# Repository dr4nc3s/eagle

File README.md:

# eagle #

My own Eagle components library as well as any PCB projects/designs I choose to work on. 

## Current Project - SAML21J breakout ##

Breakout board for using the SAML21J (yep, 64-pin). Currently putting together a list of features I want on the board. Don't want to make this too expensive, but I want enough features for me to utilize the various functions of the SAML21.

<h4>Features to Include</h4>
1. Power Supply : rails for 3.3V, 5V
2. microUSB port : for power input and programming
3. 10-pin JTAG header : for programming
4. External VREF circuitry : was told that internal VREF has a fair percentage error, so will want this out
5. Peripheral IO breakouts : breakouts specifically for some of the additional functions of the pins (I2C, UART, SPI, etc)
6. Status LEDs
7. USB-UART bridge (?) : unsure if I want this

## Future Projects ##

1. ESP32 breakout board (utilize WROOM module)
2. PIC breakout board - unsure whether I want PIC18, PIC24, or PIC32 architecture
3.

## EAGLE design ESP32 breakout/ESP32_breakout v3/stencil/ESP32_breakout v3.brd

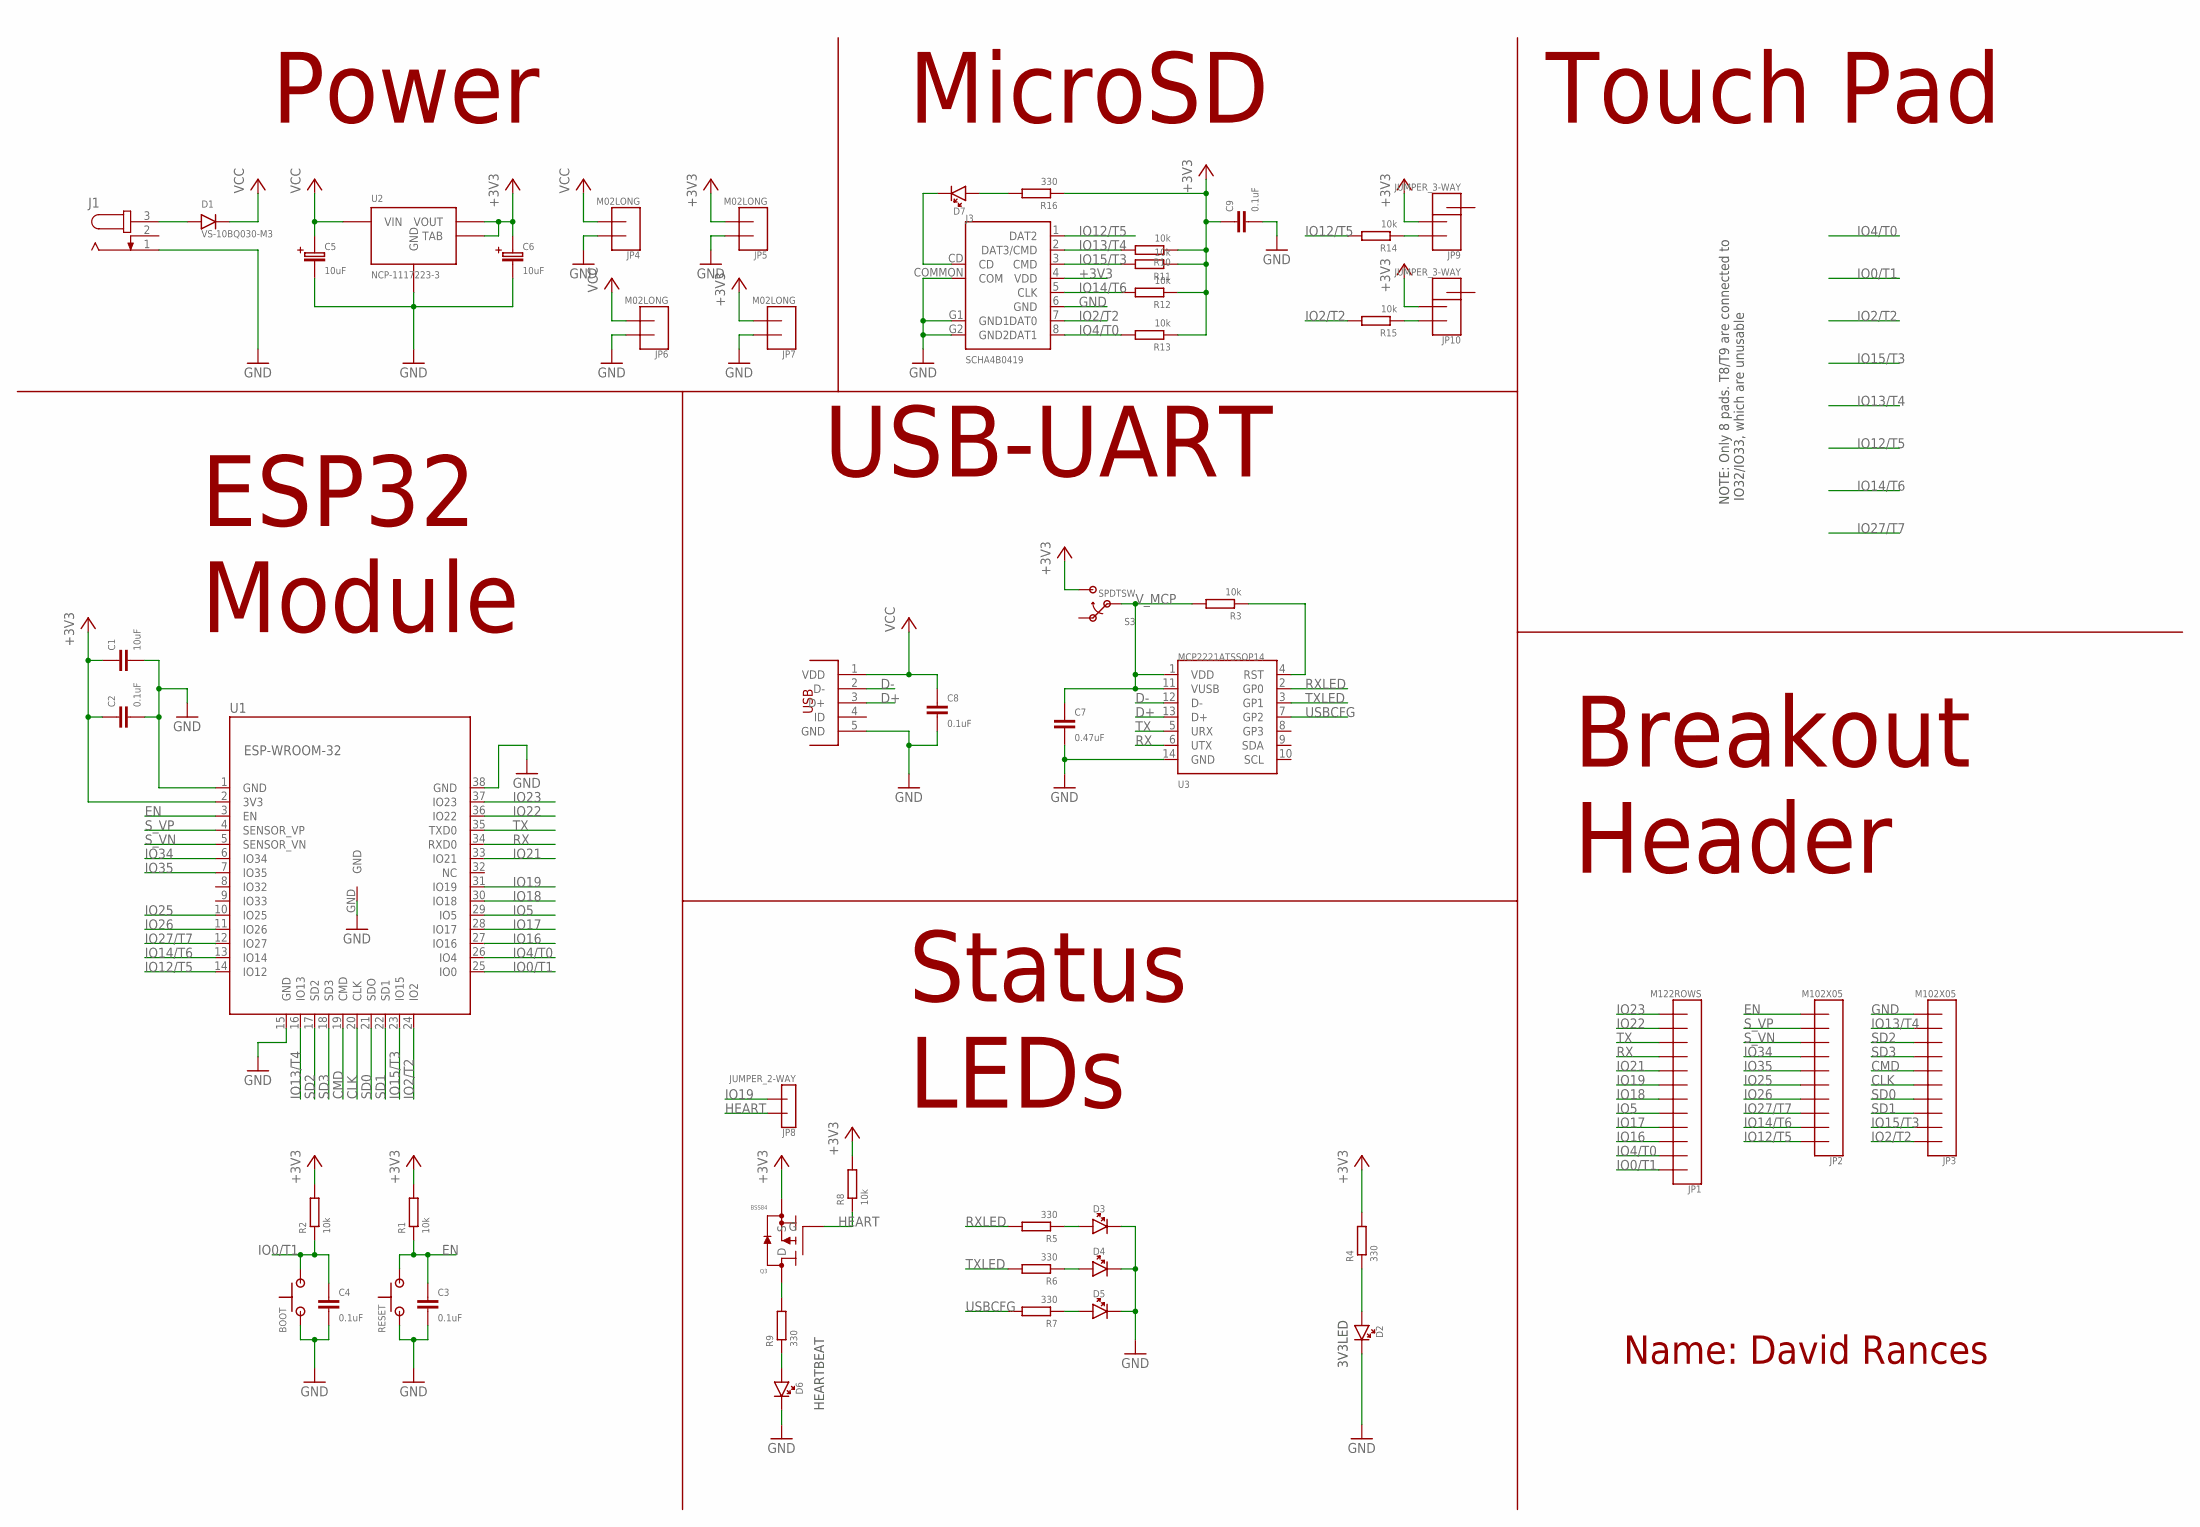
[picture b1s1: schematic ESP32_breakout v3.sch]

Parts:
BOOT: PUSHBUTTONSKHMQME010; SKHMQME010
C1: 10uF; CAP-0603
C2, C3, C4, C8, C9: 0.1uF; CAP-0603
C5, C6: 10uF; B-3528
C7: 0.47uF; CAP-0603
D1: VS-10BQ030-M3; DO-214AA
D2, D3, D4, D5, D6, D7: LED1206; LED-1206
J1: JACK-PLUG0; SPC4077
J3: SCHA4B0419; MICROSD_SCHA4B0419
JP1: M122ROWS; 2X06
JP2, JP3: M102X05; 2X05
JP4, JP5, JP6, JP7: M02LONG; 1X02-LONG
JP8: JUMPER_2-WAY; 1X02
JP9, JP10: JUMPER_3-WAY; 1X03
Q3: BSS84; SOT-23-3
R1, R2, R3, R8, R10, R11, R12, R13, R14, R15: 10k; RES-0603
R4, R5, R6, R7, R9, R16: 330; RES-0603
RESET: PUSHBUTTONSKHMQME010; SKHMQME010
S3: SPDTSW; SPDT_TH
U1: ESP-WROOM-32
U2: NCP-1117223-3; SOT-223-3
U3: MCP2221ATSSOP14; TSSOP-14
U$4: MOLEX_USBMICRO; MOLEX_47346-001

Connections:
+3V3: C1.1, C2.1, C6.P, C9.1, J3.4 (VDD), JP5.2, JP7.2, JP9.2, JP10.2, Q3.S, R1.2, R2.2, R4.2, R8.2, R10.1, R11.1, R12.1, R13.1, R16.1, S3.3 (2), U1.2 (3V3), U2.2 (VOUT), U2.PAD (TAB)
CLK: JP3.5, U1.20 (CLK)
CMD: JP3.6, U1.19 (CMD)
D+: U3.13 (D+), U$4.3 (D+)
D-: U3.12 (D-), U$4.2 (D-)
EN: C3.1, JP2.10, R1.1, RESET.3 (2), RESET.4 (2), U1.3 (EN)
GND: BOOT.1, BOOT.2 (1), C1.2, C2.2, C3.2, C4.2, C5.N, C6.N, C7.2, C8.2, C9.2, D2.C, D3.C, D4.C, D5.C, D6.C, J1.1, J3.6 (GND), J3.COMMON (COM), J3.G1 (GND1), J3.G2 (GND2), JP3.10, JP4.1, JP5.1, JP6.1, JP7.1, RESET.1, RESET.2 (1), U1.1 (GND), U1.15 (GND), U1.38 (GND), U1.GND, U2.1 (GND), U3.14 (GND), U$4.5 (GND)
HEART: JP8.1, Q3.G, R8.1
IO0/T1: BOOT.3 (2), BOOT.4 (2), C4.1, JP1.1, R2.1, U1.25 (IO0)
IO2/T2: J3.7 (DAT0), JP3.1, R15.2, U1.24 (IO2)
IO4/T0: J3.8 (DAT1), JP1.2, R13.2, U1.26 (IO4)
IO5: JP1.5, U1.29 (IO5)
IO12/T5: J3.1 (DAT2), JP2.1, R14.2, U1.14 (IO12)
IO13/T4: J3.2 (DAT3/CMD), JP3.9, R10.2, U1.16 (IO13)
IO14/T6: J3.5 (CLK), JP2.2, R12.2, U1.13 (IO14)
IO15/T3: J3.3 (CMD), JP3.2, R11.2, U1.23 (IO15)
IO16: JP1.3, U1.27 (IO16)
IO17: JP1.4, U1.28 (IO17)
IO18: JP1.6, U1.30 (IO18)
IO19: JP1.7, JP8.2, U1.31 (IO19)
IO21: JP1.8, U1.33 (IO21)
IO22: JP1.11, U1.36 (IO22)
IO23: JP1.12, U1.37 (IO23)
IO25: JP2.5, U1.10 (IO25)
IO26: JP2.4, U1.11 (IO26)
IO27/T7: JP2.3, U1.12 (IO27)
IO34: JP2.7, U1.6 (IO34)
IO35: JP2.6, U1.7 (IO35)
unnamed: D1.A, J1.3
unnamed: R3.1, U3.4 (RST)
unnamed: D5.A, R7.1
unnamed: D2.A, R4.1
unnamed: JP9.1, R14.1
unnamed: JP10.1, R15.1
unnamed: D3.A, R5.1
unnamed: D6.A, R9.1
unnamed: Q3.D, R9.2
unnamed: D4.A, R6.1
unnamed: D7.C, J3.CD
unnamed: D7.A, R16.2
RX: JP1.9, U1.34 (RXD0), U3.6 (UTX)
RXLED: R5.2, U3.2 (GP0)
SD0: JP3.4, U1.21 (SDO)
SD1: JP3.3, U1.22 (SD1)
SD2: JP3.8, U1.17 (SD2)
SD3: JP3.7, U1.18 (SD3)
S_VN: JP2.8, U1.5 (SENSOR_VN)
S_VP: JP2.9, U1.4 (SENSOR_VP)
TX: JP1.10, U1.35 (TXD0), U3.5 (URX)
TXLED: R6.2, U3.3 (GP1)
USBCFG: R7.2, U3.7 (GP2)
VCC: C5.P, C8.1, D1.C, JP4.2, JP6.2, U2.3 (VIN), U$4.1 (VDD)
V_MCP: C7.1, R3.2, S3.2 (OUT), U3.1 (VDD), U3.11 (VUSB)

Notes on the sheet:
NOTE: Only 8 pads. T8/T9 are connected to IO32/IO33, which are unusable
3V3LED
HEARTBEAT
Power
MicroSD
Touch Pad
ESP32 Module
Status LEDs
Breakout Header
USB-UART
Name: David Rances

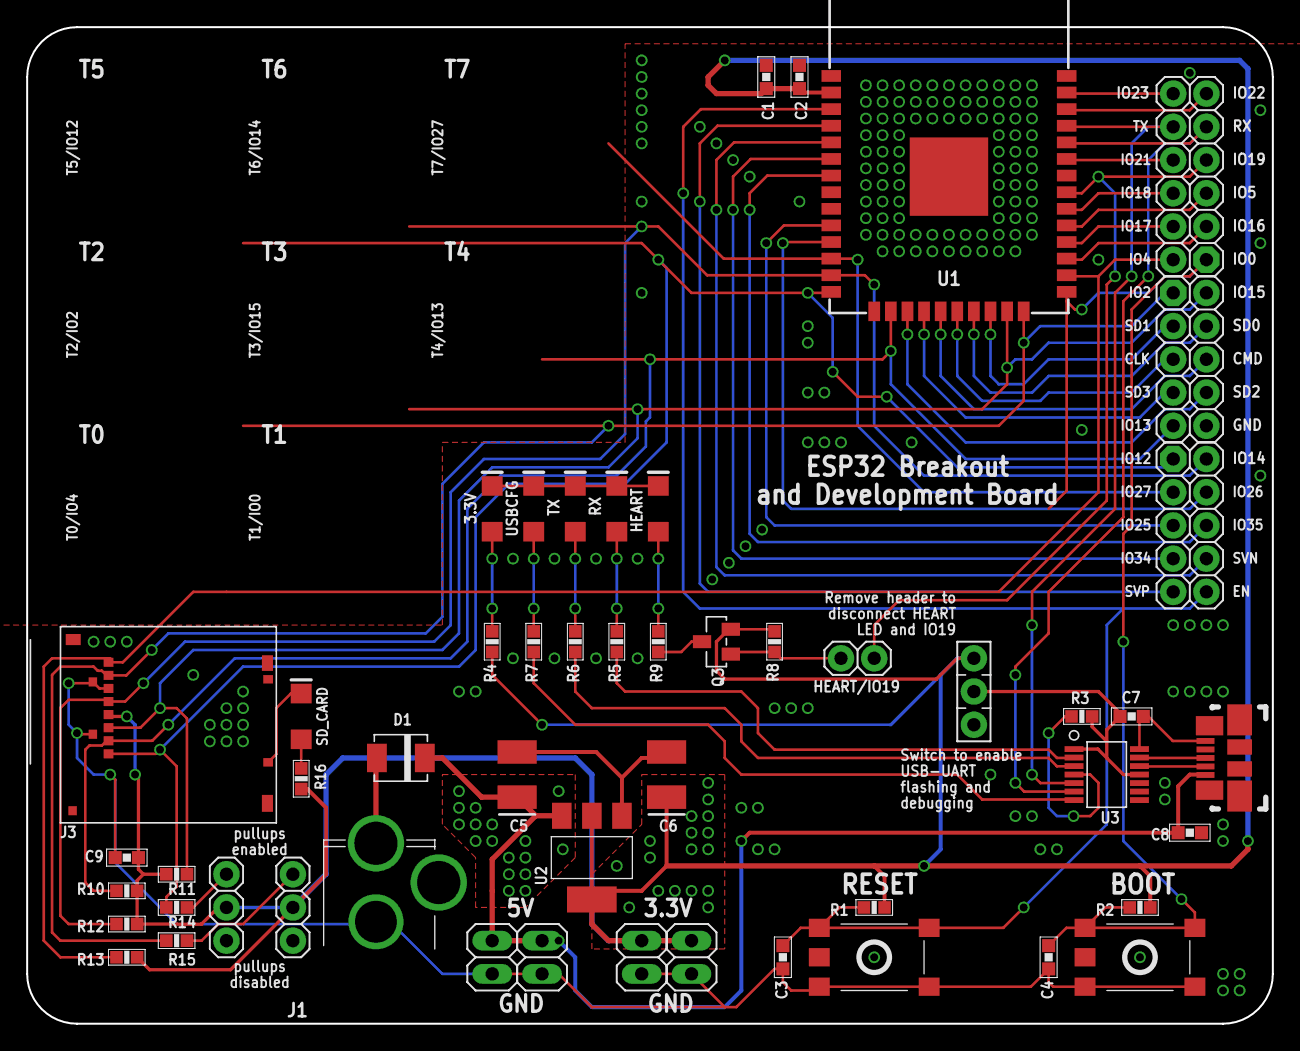
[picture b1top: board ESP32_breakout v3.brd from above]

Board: 2 copper layers, 95.2 x 76.2 mm, 52 parts (0 on the bottom side), 53 nets.

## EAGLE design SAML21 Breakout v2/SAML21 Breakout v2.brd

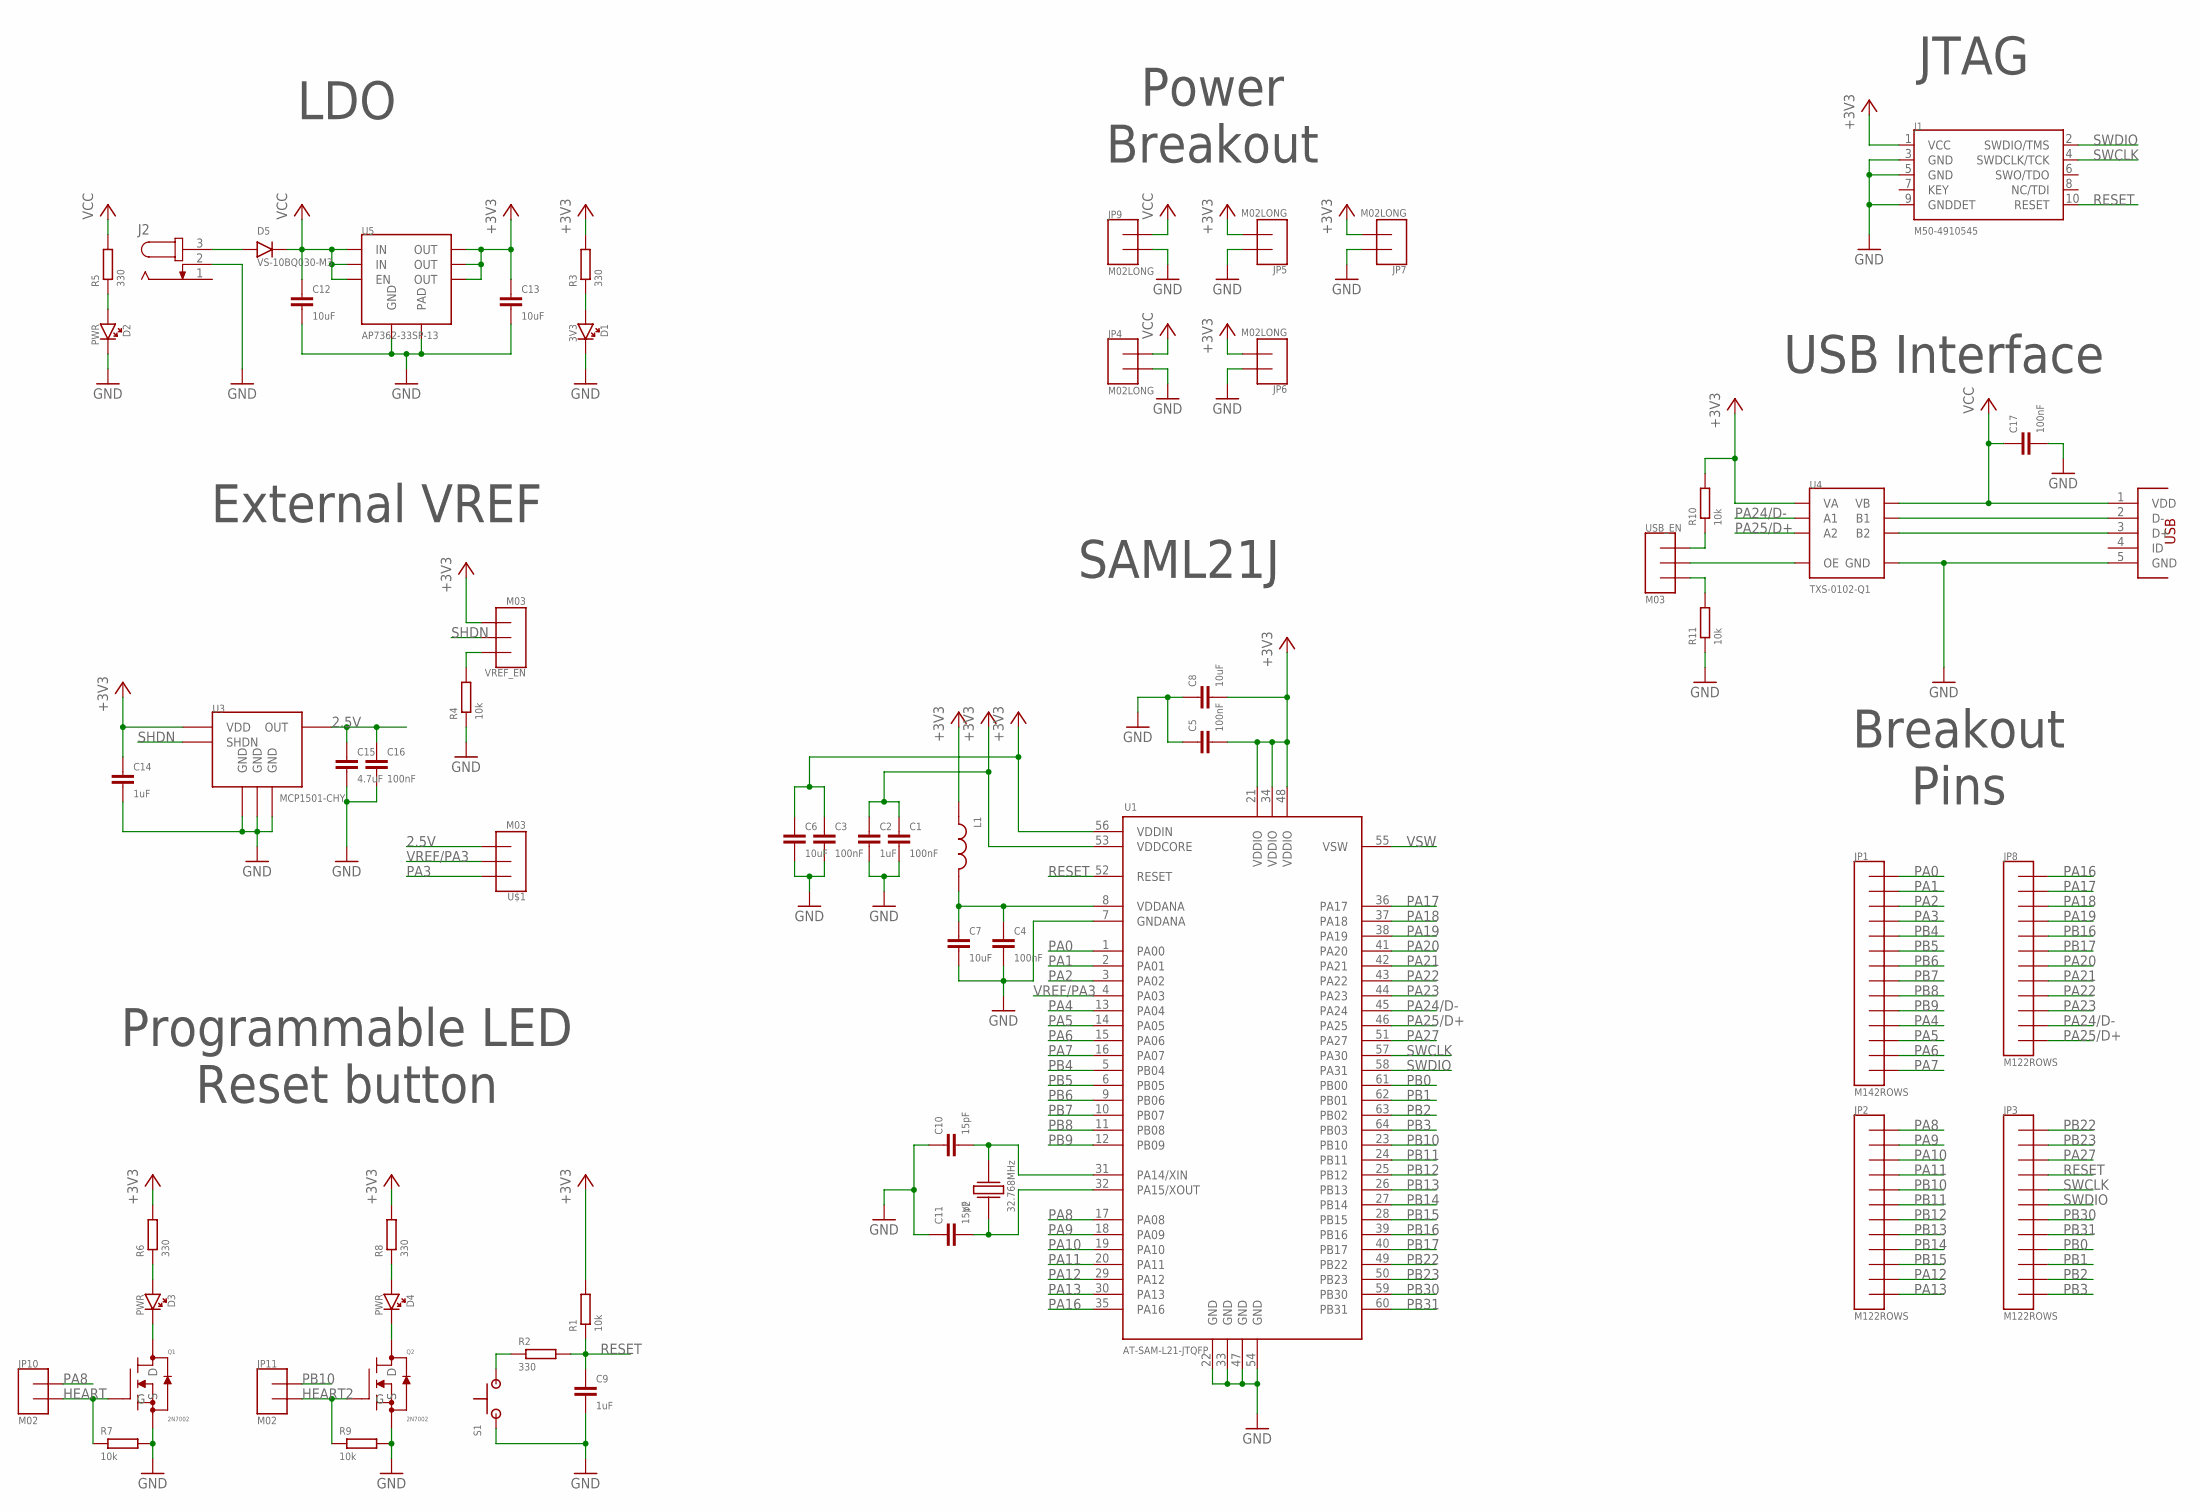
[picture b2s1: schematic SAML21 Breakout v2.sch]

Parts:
C1, C3, C4, C5, C16, C17: 100nF; CAP-0603
C2, C9, C14: 1uF; CAP-0603
C6, C7, C8, C12, C13: 10uF; CAP-0603
C10, C11: 15pF; CAP-0603
C15: 4.7uF; CAP-0805
D1: 3V3; LED-1206
D2, D3, D4: PWR; LED-1206
D5: VS-10BQ030-M3; DO-214AA
J1: M50-4910545
J2: JACK-PLUG0; SPC4077
JP1: M142ROWS; 2X07
JP2, JP3, JP8: M122ROWS; 2X06
JP4, JP5, JP6, JP7, JP9: M02LONG; 1X02-LONG
JP10, JP11: M02; 1X02
L1: INDUCTOR0603; IND-0603
Q1, Q2: 2N7002; SOT-23-3
R1, R4, R7, R9, R10, R11: 10k; RES-0805
R2, R3, R5, R6, R8: 330; RES-0805
S1: SKHMQME010
U1: AT-SAM-L21-JTQFP; TQFP-64
U3: MCP1501-CHY; SOT-23-6
U4: TXS-0102-Q1; VSSOP-8
U5: AP7362-33SP-13; SO-8EP
U$1: M03; 1X03
U$6: MOLEX_USBMICRO; MOLEX_47346-001
USB_EN: M03; 1X03
VREF_EN: M03; 1X03
Y2: 32.768MHz; CFPX-217

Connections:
2.5V: C15.1, C16.1, U3.1 (OUT), U$1.3
+3V3: C1.1, C2.1, C3.1, C5.2, C6.1, C8.2, C13.1, C14.1, J1.1 (VCC), JP5.2, JP6.2, JP7.2, L1.1, R1.2, R3.2, R6.2, R8.2, R10.2, U1.21 (VDDIO), U1.34 (VDDIO), U1.48 (VDDIO), U1.53 (VDDCORE), U1.56 (VDDIN), U3.6 (VDD), U4.3 (VA), U5.5 (OUT), U5.6 (OUT), U5.7 (OUT), VREF_EN.3
GND: C1.2, C2.2, C3.2, C4.2, C5.1, C6.2, C7.2, C8.1, C9.2, C10.1, C11.1, C12.2, C13.2, C14.2, C15.2, C16.2, C17.2, D1.C, D2.C, J1.3 (GND), J1.5 (GND), J1.9 (GNDDET), J2.2, JP4.2, JP5.1, JP6.1, JP7.1, JP9.2, Q1.S, Q2.S, R4.1, R7.2, R9.2, R11.1, S1.1, U1.7 (GNDANA), U1.22 (GND), U1.33 (GND), U1.47 (GND), U1.54 (GND), U3.2 (GND), U3.3 (GND), U3.5 (GND), U4.2 (GND), U5.1 (GND), U5.PAD, U$6.5 (GND)
HEART: JP10.2, Q1.G, R7.1
HEART2: JP11.2, Q2.G, R9.1
unnamed: R2.1, S1.3 (2)
unnamed: D1.A, R3.1
unnamed: C4.1, C7.1, L1.2, U1.8 (VDDANA)
unnamed: C10.2, U1.31 (PA14/XIN), Y2.2
unnamed: C11.2, U1.32 (PA15/XOUT), Y2.1
unnamed: D2.A, R5.1
unnamed: R4.2, VREF_EN.1
unnamed: D3.A, R6.1
unnamed: D3.C, Q1.D
unnamed: D4.A, R8.1
unnamed: D4.C, Q2.D
unnamed: D5.A, J2.3
unnamed: R10.1, USB_EN.1
unnamed: U4.8 (B1), U$6.2 (D-)
unnamed: U4.1 (B2), U$6.3 (D+)
unnamed: R11.2, USB_EN.3
unnamed: U4.6 (OE), USB_EN.2
PA0: JP1.1, U1.1 (PA00)
PA1: JP1.2, U1.2 (PA01)
PA2: JP1.3, U1.3 (PA02)
PA3: JP1.4, U$1.1
PA4: JP1.11, U1.13 (PA04)
PA5: JP1.12, U1.14 (PA05)
PA6: JP1.13, U1.15 (PA06)
PA7: JP1.14, U1.16 (PA07)
PA8: JP2.1, JP10.1, U1.17 (PA08)
PA9: JP2.2, U1.18 (PA09)
PA10: JP2.3, U1.19 (PA10)
PA11: JP2.4, U1.20 (PA11)
PA12: JP2.11, U1.29 (PA12)
PA13: JP2.12, U1.30 (PA13)
PA16: JP8.1, U1.35 (PA16)
PA17: JP8.2, U1.36 (PA17)
PA18: JP8.3, U1.37 (PA18)
PA19: JP8.4, U1.38 (PA19)
PA20: JP8.7, U1.41 (PA20)
PA21: JP8.8, U1.42 (PA21)
PA22: JP8.9, U1.43 (PA22)
PA23: JP8.10, U1.44 (PA23)
PA24/D-: JP8.11, U1.45 (PA24), U4.5 (A1)
PA25/D+: JP8.12, U1.46 (PA25), U4.4 (A2)
PA27: JP3.3, U1.51 (PA27)
PB0: JP3.9, U1.61 (PB00)
PB1: JP3.10, U1.62 (PB01)
PB2: JP3.11, U1.63 (PB02)
PB3: JP3.12, U1.64 (PB03)
PB4: JP1.5, U1.5 (PB04)
PB5: JP1.6, U1.6 (PB05)
PB6: JP1.7, U1.9 (PB06)
PB7: JP1.8, U1.10 (PB07)
PB8: JP1.9, U1.11 (PB08)
PB9: JP1.10, U1.12 (PB09)
PB10: JP2.5, JP11.1, U1.23 (PB10)
PB11: JP2.6, U1.24 (PB11)
PB12: JP2.7, U1.25 (PB12)
PB13: JP2.8, U1.26 (PB13)
PB14: JP2.9, U1.27 (PB14)
PB15: JP2.10, U1.28 (PB15)
PB16: JP8.5, U1.39 (PB16)
PB17: JP8.6, U1.40 (PB17)
PB22: JP3.1, U1.49 (PB22)
PB23: JP3.2, U1.50 (PB23)
PB30: JP3.7, U1.59 (PB30)
PB31: JP3.8, U1.60 (PB31)
RESET: C9.1, J1.10 (RESET), JP3.4, R1.1, R2.2, U1.52 (RESET)
SHDN: U3.4 (SHDN), VREF_EN.2
SWCLK: J1.4 (SWDCLK/TCK), JP3.5, U1.57 (PA30)
SWDIO: J1.2 (SWDIO/TMS), JP3.6, U1.58 (PA31)
VCC: C12.1, C17.1, D5.C, JP4.1, JP9.1, R5.2, U4.7 (VB), U5.2 (EN), U5.3 (IN), U5.4 (IN), U$6.1 (VDD)
VREF/PA3: U1.4 (PA03), U$1.2
VSW: U1.55 (VSW)

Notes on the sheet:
SAML21J
Breakout Pins
JTAG
Power Breakout
LDO
External VREF
Programmable LED Reset button
USB Interface

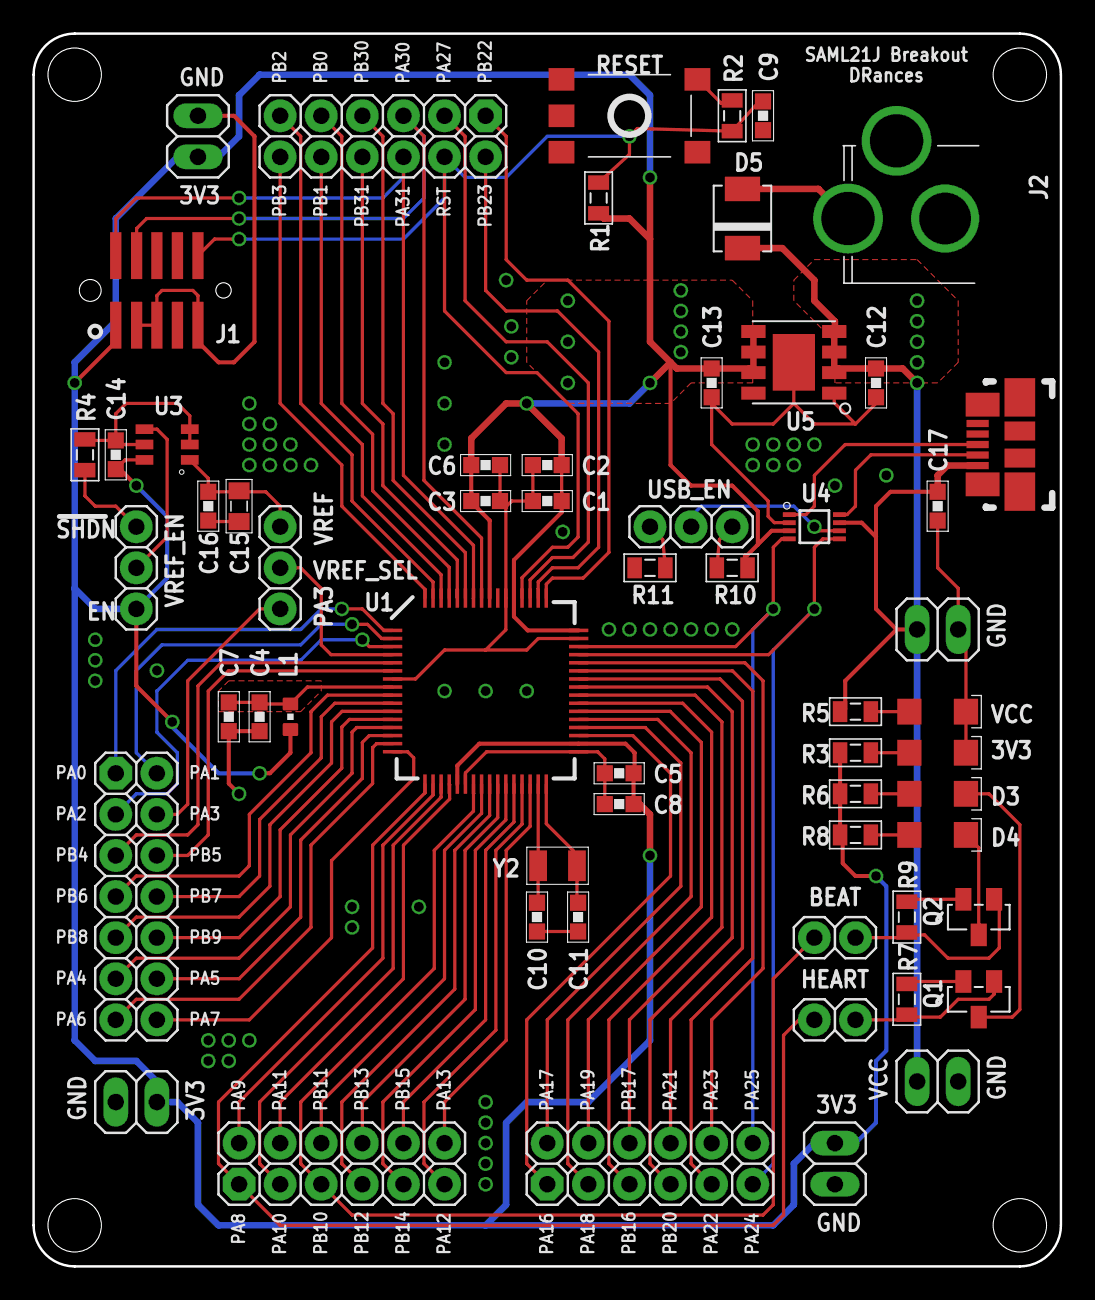
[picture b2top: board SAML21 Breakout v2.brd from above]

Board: 2 copper layers, 63.5 x 76.2 mm, 63 parts (0 on the bottom side), 75 nets.

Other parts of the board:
U$2, U$3, U$4, U$5: STAND-OFF-HOLE

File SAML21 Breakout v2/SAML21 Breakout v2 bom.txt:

Partlist exported from C:/Users/Mobile Me/Documents/GitHub/eagle/SAML21 Breakout v1/SAML21 Breakout.sch at 6/23/2017 11:00 AM

Qty Value            Device           Package         Parts                    Description                               
1                    INDUCTOR0603     IND-0603        L1                                                                 ===
1                    JACK-PLUG0       SPC4077         J2                       DC POWER JACK                             ===
1                    SKHMQME010       SKHMQME010      S1                       ALPS Tactile Switch                       ===
6   100nF            CAP0603          CAP-0603        C1, C3, C4, C5, C16, C17 Multilayer Ceramic Capacitor              ===
6   10k              RESISTOR0805     RES-0805        R1, R4, R7, R9, R10, R11                                           ===
5   10uF             CAP0603          CAP-0603        C6, C7, C8, C12, C13     Multilayer Ceramic Capacitor              ===
2   15pF             CAP0603          CAP-0603        C10, C11                 Multilayer Ceramic Capacitor              
3   1uF              CAP0603          CAP-0603        C2, C9, C14              Multilayer Ceramic Capacitor              ===
2   2N7002           2N7002           SOT-23-3        Q1, Q2                   Fairchild ON Semiconductor                ===
1   32.768MHz        LFXTAL054236-R   CFPX-217        Y2                       Crystal 32.768MHz                         ===
5   330              RESISTOR0805     RES-0805        R2, R3, R5, R6, R8                                                 ===
1   3V3              LED1206          LED-1206        D1                                                                 ===
1   4.7uF            CAP0603          CAP-0603        C15                      Multilayer Ceramic Capacitor              ===
1   AP7362-33SP-13   AP7362-33SP-13   SO-8EP          U5                       Diodes Inc.                               ===
1   AT-SAM-L21-JTQFP AT-SAM-L21-JTQFP TQFP-64         U1                       Atmel/Microchip SAML21 Series, 64-pin     ===
2   M02              M02              1X02            JP10, JP11                                                         
5   M02LONG          M02LONG          1X02-LONG       JP4, JP5, JP6, JP7, JP9                                            
3   M03              M03              1X03            U$1, USB_EN, VREF_EN                                               
3   M122ROWS         M122ROWS         2X06            JP2, JP3, JP8                                                      
1   M142ROWS         M142ROWS         2X07            JP1                                                                ===
1   M50-4910545      M50-4910545      M50-4910545     J1                       Harwin 10-pin Connector                   
1   MCP1501-CHY      MCP1501-CHY      SOT-23-6        U3                       High Precision Buffered Voltage Reference ===
1   MOLEX_USBMICRO   MOLEX_USBMICRO   MOLEX_47346-001 U$6                                                                ===
3   PWR              LED1206          LED-1206        D2, D3, D4                                                         
1   TXS-0102-Q1      TXS-0102-Q1      VSSOP-8         U4                       Texas Instruments                         ===
1   VS-10BQ030-M3    VS-10BQ030-M3    DO-214AA        D5                       Vishay Semiconductors

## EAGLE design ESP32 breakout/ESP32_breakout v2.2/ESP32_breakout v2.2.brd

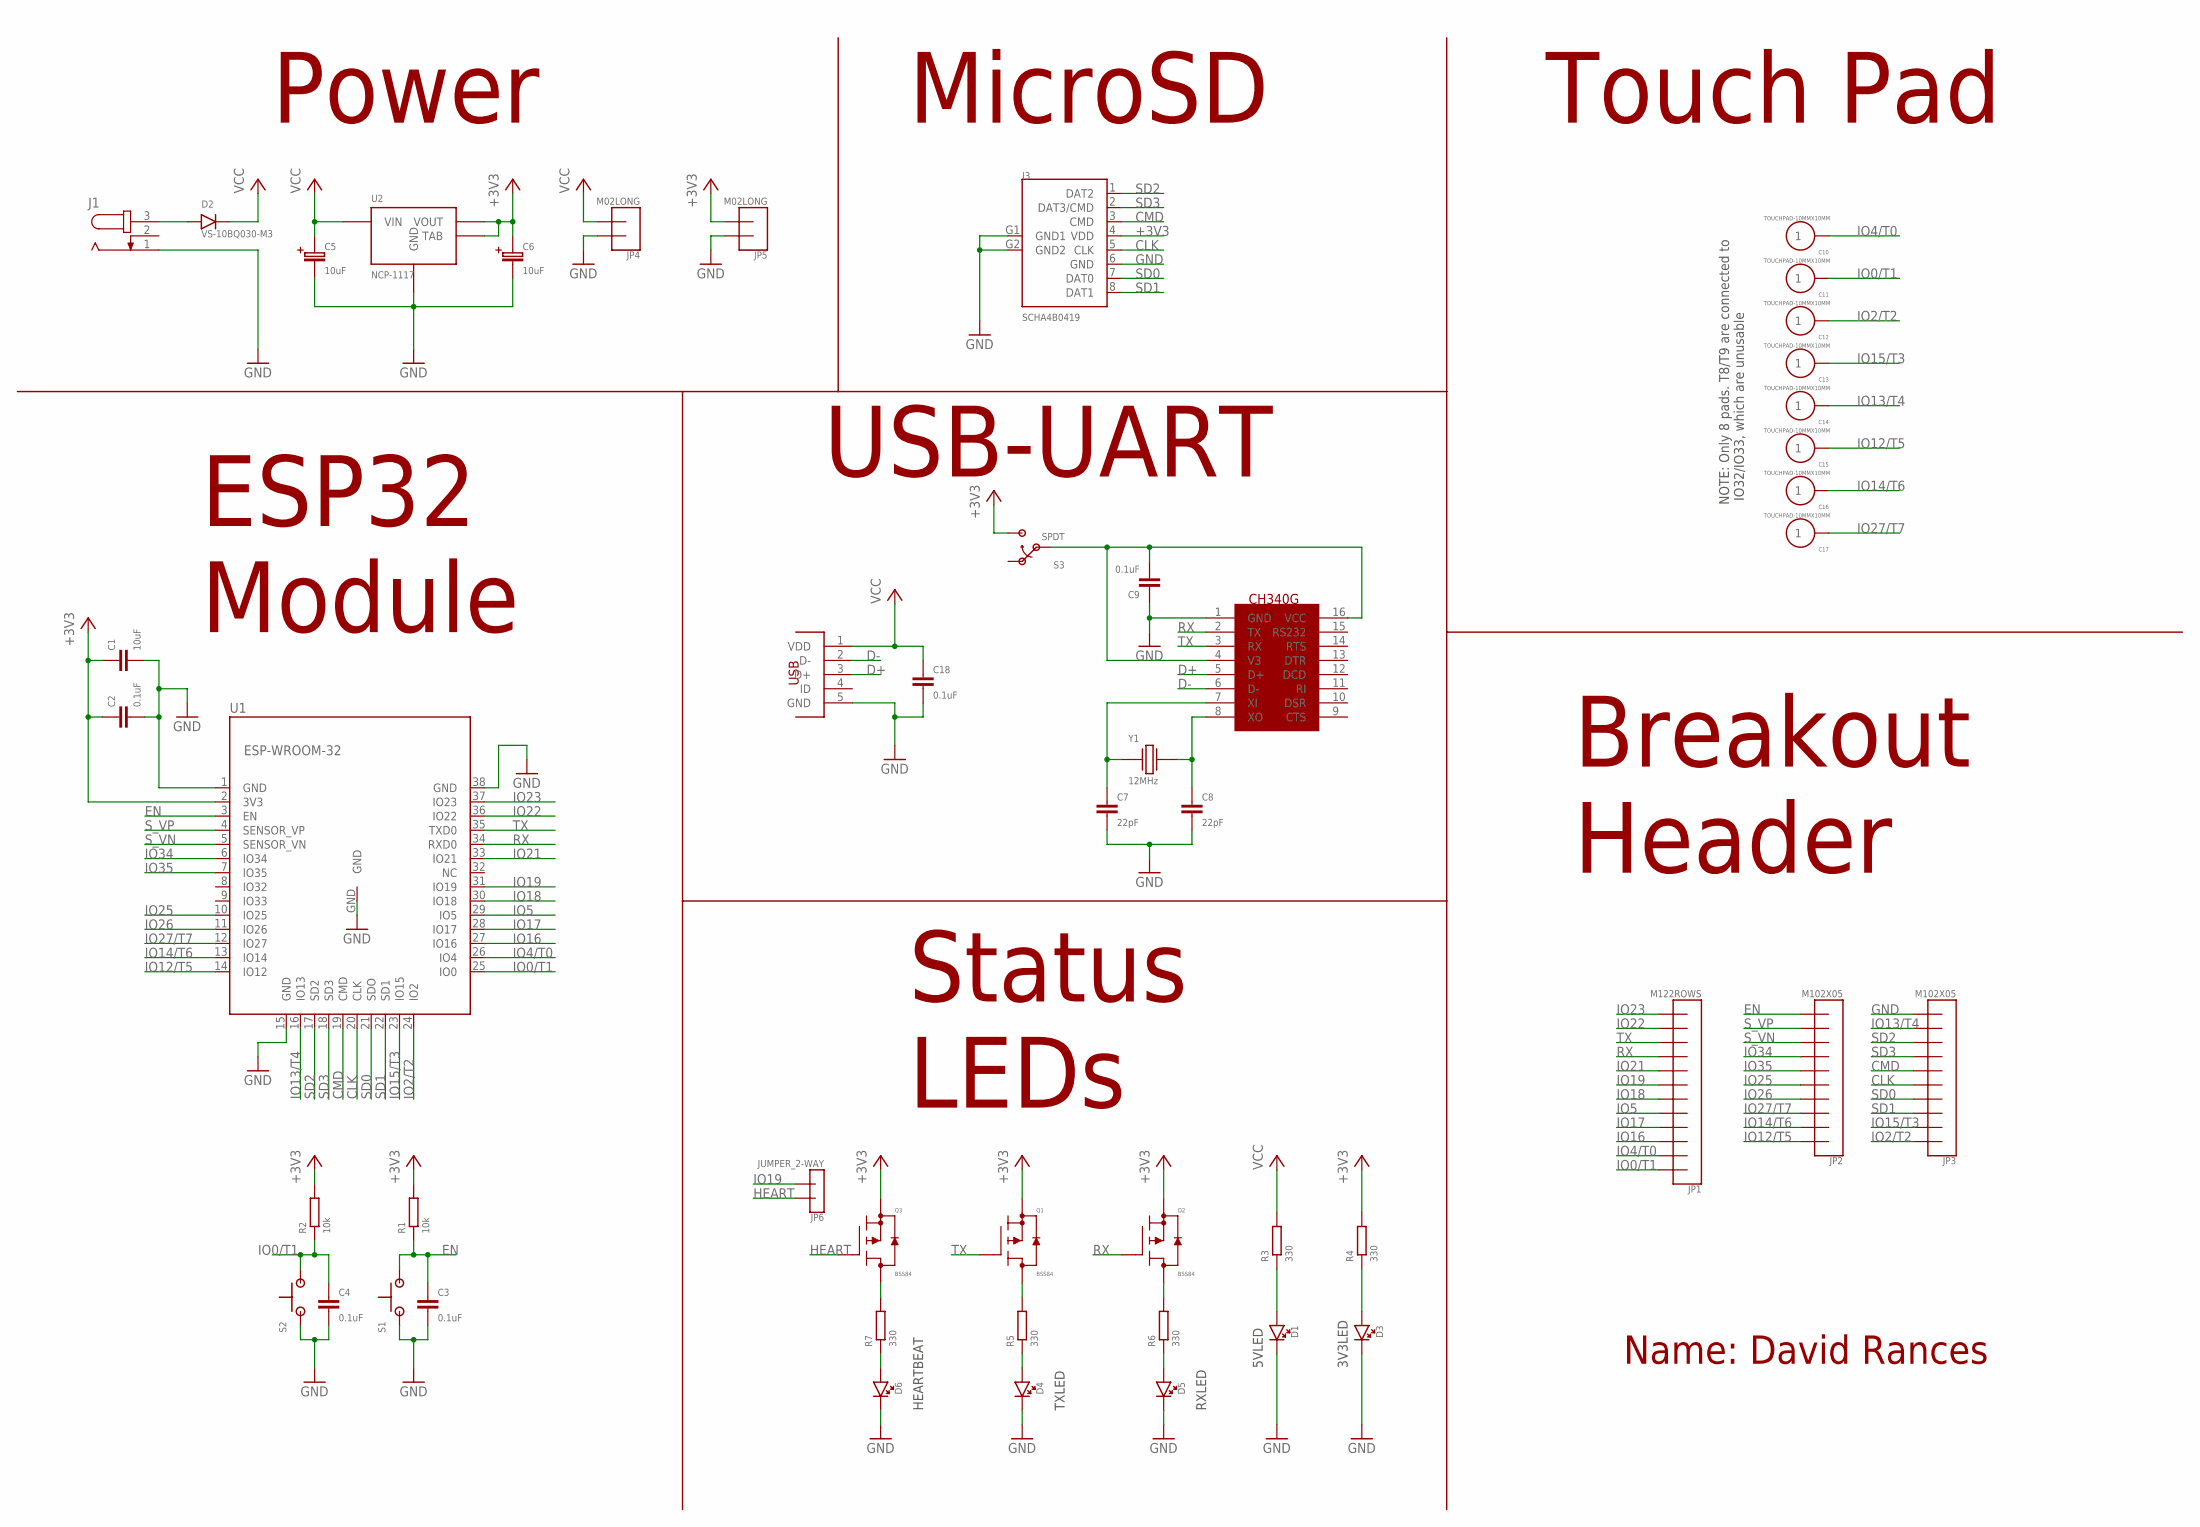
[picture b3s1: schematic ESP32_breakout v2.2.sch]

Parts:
C1: 10uF; CAP-0603
C2, C3, C4, C9, C18: 0.1uF; CAP-0603
C5, C6: 10uF; B-3528
C7, C8: 22pF; CAP-0603
C10, C11, C12, C13, C14, C15, C16, C17: TOUCHPAD-10MMX10MM; TOUCH-10MMX10MM
D1, D3, D4, D5, D6: LED1206; LED-1206
D2: VS-10BQ030-M3; DO-214AA
J1: JACK-PLUG0; SPC4077
J3: SCHA4B0419; MICROSD_SCHA4B0419
JP1: M122ROWS; 2X06
JP2, JP3: M102X05; 2X05
JP4, JP5: M02LONG; 1X02-LONG
JP6: JUMPER_2-WAY; 1X02
Q1, Q2, Q3: BSS84; SOT-23-3
R1, R2: 10k; RES-0603
R3, R4, R5, R6, R7: 330; RES-0805
S1, S2: PUSHBUTTONSKHMQME010; SKHMQME010
S3: SPDT; 1X03
U1: ESP-WROOM-32
U2: NCP-1117; SOT-223-4
U$4: MOLEX_USBMICRO; MOLEX_47346-001
U$7: CH340G; SOIC16
Y1: 12MHz; HC-49/US

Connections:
+3V3: C1.1, C2.1, C6.P, J3.4 (VDD), JP5.2, Q1.S, Q2.S, Q3.S, R1.2, R2.2, R4.2, S3.3 (2), U1.2 (3V3), U2.2 (VOUT), U2.PAD (TAB)
CLK: J3.5 (CLK), JP3.5, U1.20 (CLK)
CMD: J3.3 (CMD), JP3.6, U1.19 (CMD)
D+: U$4.3 (D+), U$7.5 (D+)
D-: U$4.2 (D-), U$7.6 (D-)
EN: C3.1, JP2.10, R1.1, S1.3 (2), S1.4 (2), U1.3 (EN)
GND: C1.2, C2.2, C3.2, C4.2, C5.N, C6.N, C7.2, C8.2, C9.1, C18.2, D1.C, D3.C, D4.C, D5.C, D6.C, J1.1, J3.6 (GND), J3.G1 (GND1), J3.G2 (GND2), JP3.10, JP4.1, JP5.1, S1.1, S1.2 (1), S2.1, S2.2 (1), U1.1 (GND), U1.15 (GND), U1.38 (GND), U1.GND, U2.1 (GND), U$4.5 (GND), U$7.1 (GND)
HEART: JP6.1, Q3.G
IO0/T1: C4.1, C11.P$1, JP1.1, R2.1, S2.3 (2), S2.4 (2), U1.25 (IO0)
IO2/T2: C12.P$1, JP3.1, U1.24 (IO2)
IO4/T0: C10.P$1, JP1.2, U1.26 (IO4)
IO5: JP1.5, U1.29 (IO5)
IO12/T5: C15.P$1, JP2.1, U1.14 (IO12)
IO13/T4: C14.P$1, JP3.9, U1.16 (IO13)
IO14/T6: C16.P$1, JP2.2, U1.13 (IO14)
IO15/T3: C13.P$1, JP3.2, U1.23 (IO15)
IO16: JP1.3, U1.27 (IO16)
IO17: JP1.4, U1.28 (IO17)
IO18: JP1.6, U1.30 (IO18)
IO19: JP1.7, JP6.2, U1.31 (IO19)
IO21: JP1.8, U1.33 (IO21)
IO22: JP1.11, U1.36 (IO22)
IO23: JP1.12, U1.37 (IO23)
IO25: JP2.5, U1.10 (IO25)
IO26: JP2.4, U1.11 (IO26)
IO27/T7: C17.P$1, JP2.3, U1.12 (IO27)
IO34: JP2.7, U1.6 (IO34)
IO35: JP2.6, U1.7 (IO35)
unnamed: D1.A, R3.1
unnamed: D2.A, J1.3
unnamed: C7.1, U$7.7 (XI), Y1.P$1 (1)
unnamed: C8.1, U$7.8 (XO), Y1.P$2 (2)
unnamed: D3.A, R4.1
unnamed: Q1.D, R5.2
unnamed: Q2.D, R6.2
unnamed: D4.A, R5.1
unnamed: D6.A, R7.1
unnamed: Q3.D, R7.2
unnamed: D5.A, R6.1
unnamed: C9.2, S3.2 (OUT), U$7.4 (V3), U$7.16 (VCC)
RX: JP1.9, Q2.G, U1.34 (RXD0), U$7.2 (TX)
SD0: J3.7 (DAT0), JP3.4, U1.21 (SDO)
SD1: J3.8 (DAT1), JP3.3, U1.22 (SD1)
SD2: J3.1 (DAT2), JP3.8, U1.17 (SD2)
SD3: J3.2 (DAT3/CMD), JP3.7, U1.18 (SD3)
S_VN: JP2.8, U1.5 (SENSOR_VN)
S_VP: JP2.9, U1.4 (SENSOR_VP)
TX: JP1.10, Q1.G, U1.35 (TXD0), U$7.3 (RX)
VCC: C5.P, C18.1, D2.C, JP4.2, R3.2, U2.3 (VIN), U$4.1 (VDD)

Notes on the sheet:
NOTE: Only 8 pads. T8/T9 are connected to IO32/IO33, which are unusable
5VLED
3V3LED
TXLED
RXLED
HEARTBEAT
Power
MicroSD
Touch Pad
ESP32 Module
Status LEDs
Breakout Header
USB-UART
Name: David Rances
